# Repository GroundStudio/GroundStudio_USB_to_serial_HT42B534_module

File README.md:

GroundStudio USB to serial HT42B534 Module
====================================

Get it from [ardushop.ro](https://ardushop.ro/ro/home/1725-usbttlht42b534-2.html)

Explore all the GroundStudio products at [GroundStudio.ro](https://groundstudio.ro/)

Description
-------------------
USB to serial module based on HT42B534-2 chip.

Contents
-------------------

* [/Documentation](https://github.com/GroundStudio/GroundStudio_USB_to_serial_HT42B534_module/tree/main/Documentation) -- Contains documentation written during creation of this repository, with readme.md index of its own!
* [/Firmware](https://github.com/GroundStudio/GroundStudio_USB_to_serial_HT42B534_module/tree/main/Firmware) -- Firmware (bootloaders, etc)
* [/Hardware](https://github.com/GroundStudio/GroundStudio_USB_to_serial_HT42B534_module/tree/main/Hardware) -- Schematics, layout.
* [/Libraries](https://github.com/GroundStudio/GroundStudio_USB_to_serial_HT42B534_module/tree/main/Libraries) -- Arduino/CircuitPython libraries. 
* [/Tools](https://github.com/GroundStudio/GroundStudio_USB_to_serial_HT42B534_module/tree/main) -- Tools needed for compiling, uploading bootloader, etc.

Versions
-------------------
*(Not all tags shown)*
* [V0.2] Initial version

License
-------------------

This is released under the [Attribution-ShareAlike 4.0 International (CC BY-SA 4.0)](https://creativecommons.org/licenses/by-sa/4.0/) license. 
**You are welcome to use this for commercial purposes.**

Please consider contributing back to this project or others to help the open-source hardware community continue to thrive and grow! 

Certifications:

[Open Source Hardware Association](https://certification.oshwa.org/ro000011.html)   
   
[
](https://certification.oshwa.org/ro000011.html)

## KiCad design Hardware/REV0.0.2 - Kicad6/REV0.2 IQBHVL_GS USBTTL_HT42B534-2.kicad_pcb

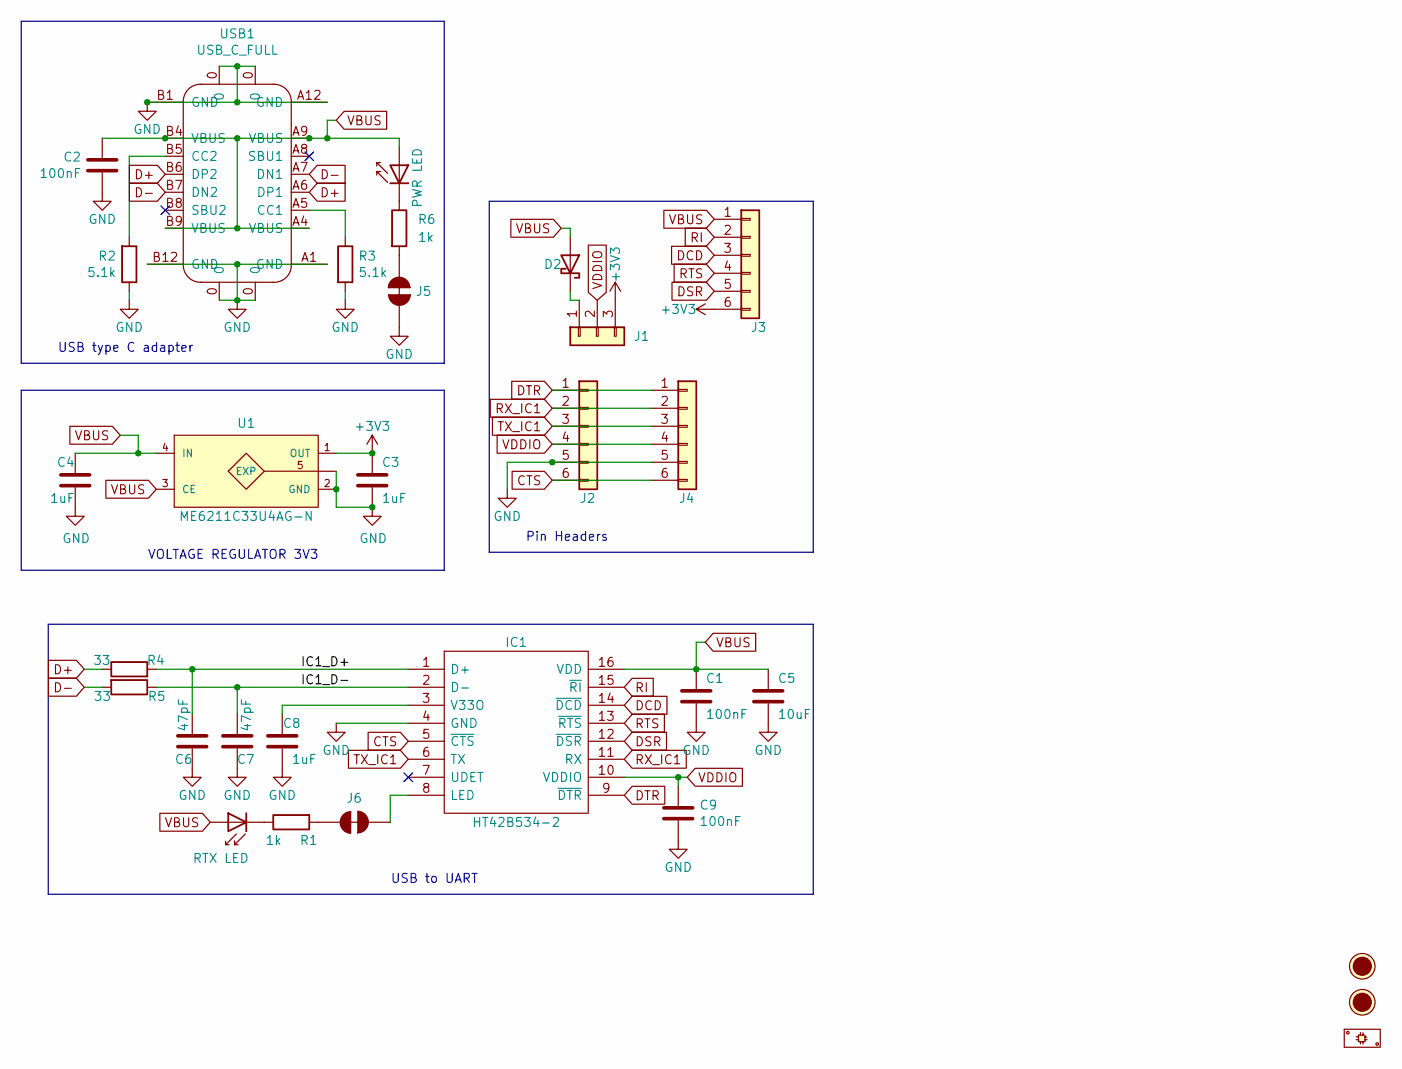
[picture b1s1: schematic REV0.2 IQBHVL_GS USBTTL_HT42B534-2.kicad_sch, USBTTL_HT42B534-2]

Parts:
C1, C2, C9: 100nF; C_0402_1005Metric; MPN 0402B104K100CT; LCSC C387941
C3, C4, C8: 1uF; C_0402_1005Metric; MPN FS15B105K100PKG; LCSC C525324
C5: 10uF; C_0402_1005Metric; MPN LDK105CBJ106MVLF; LCSC C386033
C6, C7: 47pF; C_0402_1005Metric; MPN FN15N470J500PNG; LCSC C525215
D1: RTX LED; LED_0402_1005Metric; MPN TZ-P2-0402GTIA1-0.45T; LCSC C688877
D2: D_Schottky; SOD-323; MPN SD103AWS; LCSC C438010
D3: PWR LED; LED_0402_1005Metric; MPN TZ-P2-0402RTIA1-0.45T; LCSC C779449
FID1, FID2: Fiducial; Fiducial_1mm_Mask2mm
IC1: HT42B534-2; SOP-16_150MIL; MPN HT42B534-2; LCSC C493361
J1: Conn_Male; PinHeader_1x03_P2.54mm_Vertical_Male; MPN C49257; LCSC C49257
J2: Conn_Female; PinHeader_1x06_P2.54mm_Vertical_Female; MPN C124415; LCSC C124415
J3, J4: Conn_Male; PinHeader_1x06_P2.54mm_Vertical_Male; MPN C37208; LCSC C37208
J5: PWR LED DISABLE; SolderJumper_NC
J6: SolderJumper_NC
P1: PCB; MPN IQBHVL_GS_PCB
R1, R6: 1k; R_0402_1005Metric; MPN RC-02W1001FT; LCSC C226166
R2, R3: 5.1k; R_0402_1005Metric; MPN RC-02W5101FT; LCSC C294638
R4, R5: 33; R_0402_1005Metric; MPN RC-02W33R0FT; LCSC C140161
U1: ME6211C33U4AG-N; FBP1-1-4; MPN ME6211C33U4AG-N; LCSC C428904
USB1: USB_C_FULL; USB_C_C167321; MPN 918-418K2023S40001; LCSC C167321

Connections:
+3V3: C3.1, J1.3, J3.6, U1.1 (OUT)
/IC1_D+: C6.1, IC1.1 (D+), R4.2
/IC1_D-: C7.1, IC1.2 (D-), R5.1
CTS: IC1.5 (~CTS), J2.6, J4.6
D+: R4.1, USB1.A6 (DP1), USB1.B6 (DP2)
D-: R5.2, USB1.A7 (DN1), USB1.B7 (DN2)
DCD: IC1.14 (~DCD), J3.3
DSR: IC1.12 (~DSR), J3.5
DTR: IC1.9 (~DTR), J2.1, J4.1
GND: C1.2, C2.1, C3.2, C4.2, C5.2, C6.2, C7.2, C8.2, C9.2, IC1.4 (GND), J2.5, J4.5, J5.1, R2.1, R3.2, U1.2 (GND), U1.5 (EXP), USB1.0, USB1.A1 (GND), USB1.A12 (GND), USB1.B1 (GND), USB1.B12 (GND)
unnamed: C8.1, IC1.3 (V33O)
unnamed: D1.1 (K), R1.1
unnamed: D2.1 (K), J1.1
unnamed: D3.1 (K), R6.1
unnamed: IC1.8 (LED), J6.1
unnamed: J5.2, R6.2
unnamed: J6.2, R1.2
unnamed: R2.2, USB1.B5 (CC2)
unnamed: R3.1, USB1.A5 (CC1)
RI: IC1.15 (~RI), J3.2
RTS: IC1.13 (~RTS), J3.4
RX_IC1: IC1.11 (RX), J2.2, J4.2
TX_IC1: IC1.6 (TX), J2.3, J4.3
VBUS: C1.1, C2.2, C4.1, C5.1, D1.2 (A), D2.2 (A), D3.2 (A), IC1.16 (VDD), J3.1, U1.3 (CE), U1.4 (IN), USB1.A4 (VBUS), USB1.A9 (VBUS), USB1.B4 (VBUS), USB1.B9 (VBUS)
VDDIO: C9.1, IC1.10 (VDDIO), J1.2, J2.4, J4.4

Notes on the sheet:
USB to UART
USB type C adapter
Pin Headers
VOLTAGE REGULATOR 3V3

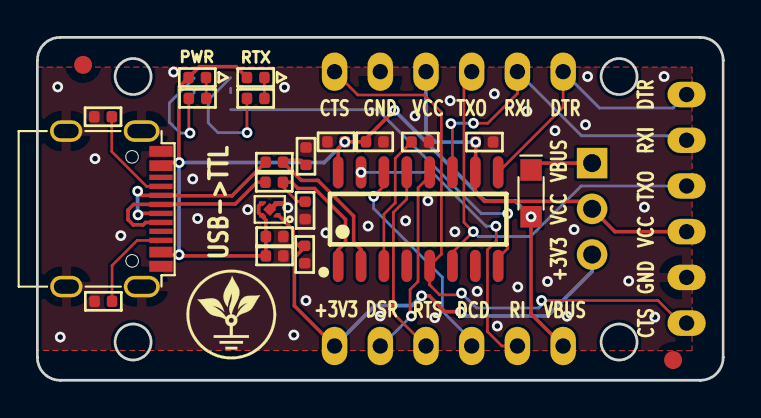
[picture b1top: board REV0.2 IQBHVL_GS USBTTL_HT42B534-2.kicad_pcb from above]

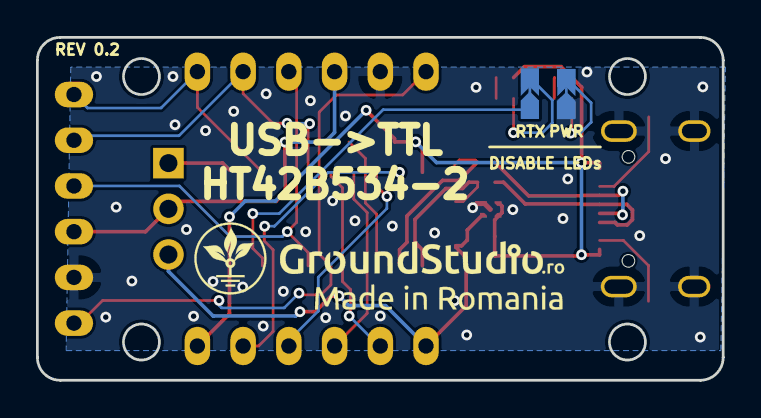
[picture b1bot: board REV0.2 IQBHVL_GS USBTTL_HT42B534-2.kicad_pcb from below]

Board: 2 copper layers, 38.1 x 19.1 mm, 29 parts (4 on the bottom side), 25 nets.

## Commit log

2023-10-24 - first commit
2023-10-24 - added schematic pdf and kicad 6 files
2023-11-03 - added datasheet
